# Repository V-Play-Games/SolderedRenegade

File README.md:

# SolderedRenegade

It's a Giratina which has 2 LEDs as eyes, controlled by a switch on the back!

## Author
Vaibhav Nargwani aka [@V Play Games](https://hackclub.slack.com/team/U08RM94EECT)

## Bill of Materials
| S. No.  | Name           | Quantity |
| ------- | -------------- | -------- |
| 1       | Battery Holder | 1        |
| 2       | Push Button    | 1        |
| 3       | 5mm LED        | 2        |
| 4       | Resistor       | 6        |

## Schematic

## PCB

## 3D View

Built for [Solder](https://solder.hackclub.com)!

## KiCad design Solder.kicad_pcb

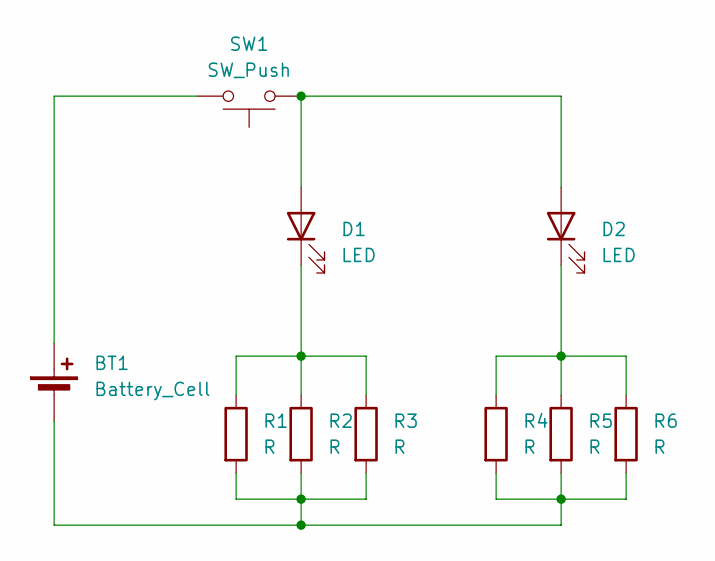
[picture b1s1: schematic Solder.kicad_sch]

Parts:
BT1: Battery_Cell; BatteryHolder_Keystone_3034_1x20mm
D1, D2: LED; LED_D5.0mm
R1, R2, R3, R4, R5, R6: R; R_Axial_DIN0207_L6.3mm_D2.5mm_P7.62mm_Horizontal
SW1: SW_Push; SW_PUSH_6mm

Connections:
unnamed: BT1.1 (+), SW1.2
unnamed: BT1.2 (-), R1.2, R2.2, R3.2, R4.2, R5.2, R6.2
unnamed: D1.2 (A), D2.2 (A), SW1.1
unnamed: D1.1 (K), R1.1, R2.1, R3.1
unnamed: D2.1 (K), R4.1, R5.1, R6.1

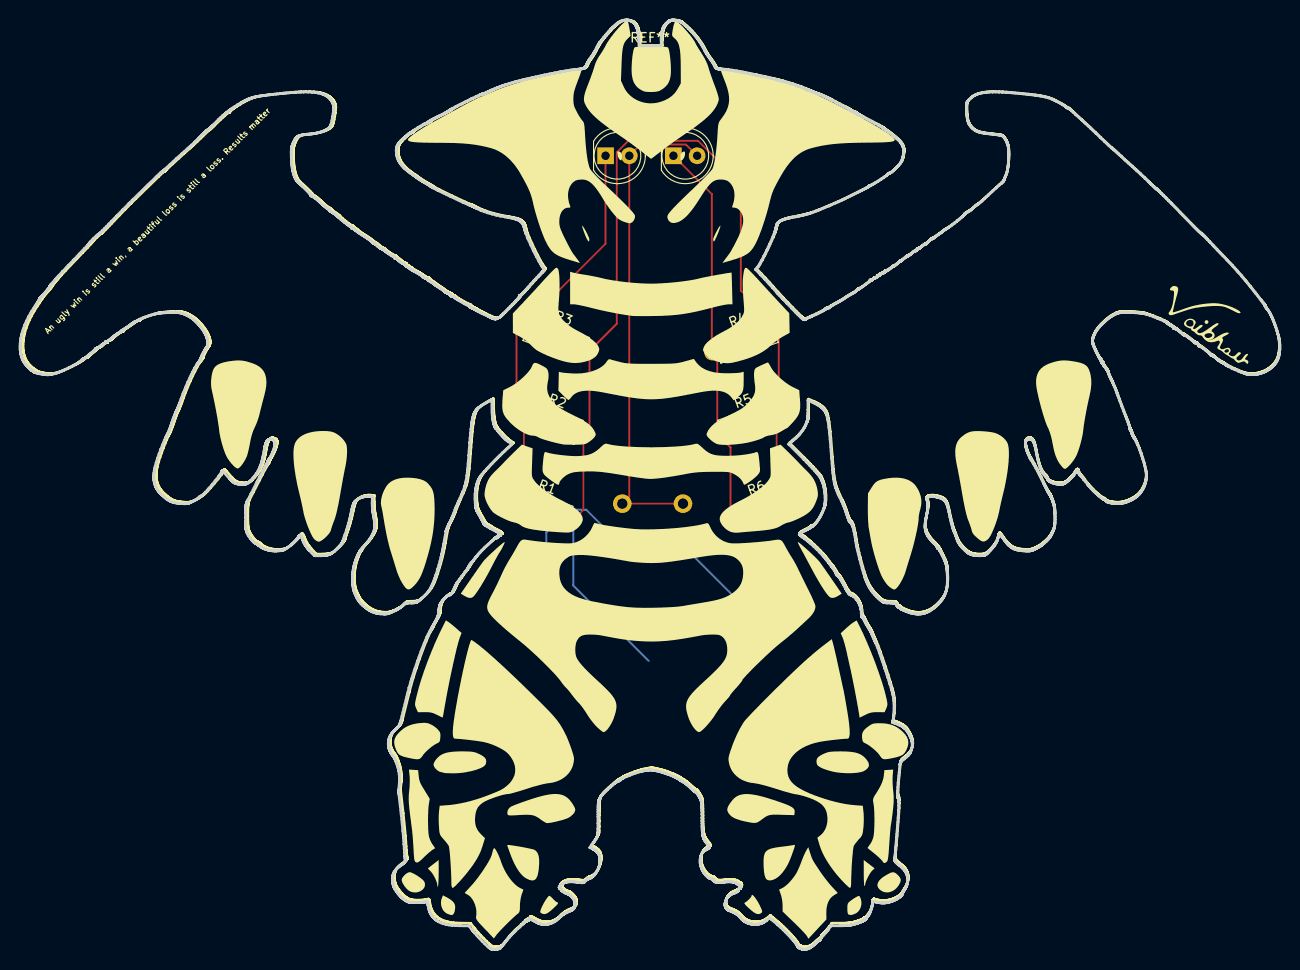
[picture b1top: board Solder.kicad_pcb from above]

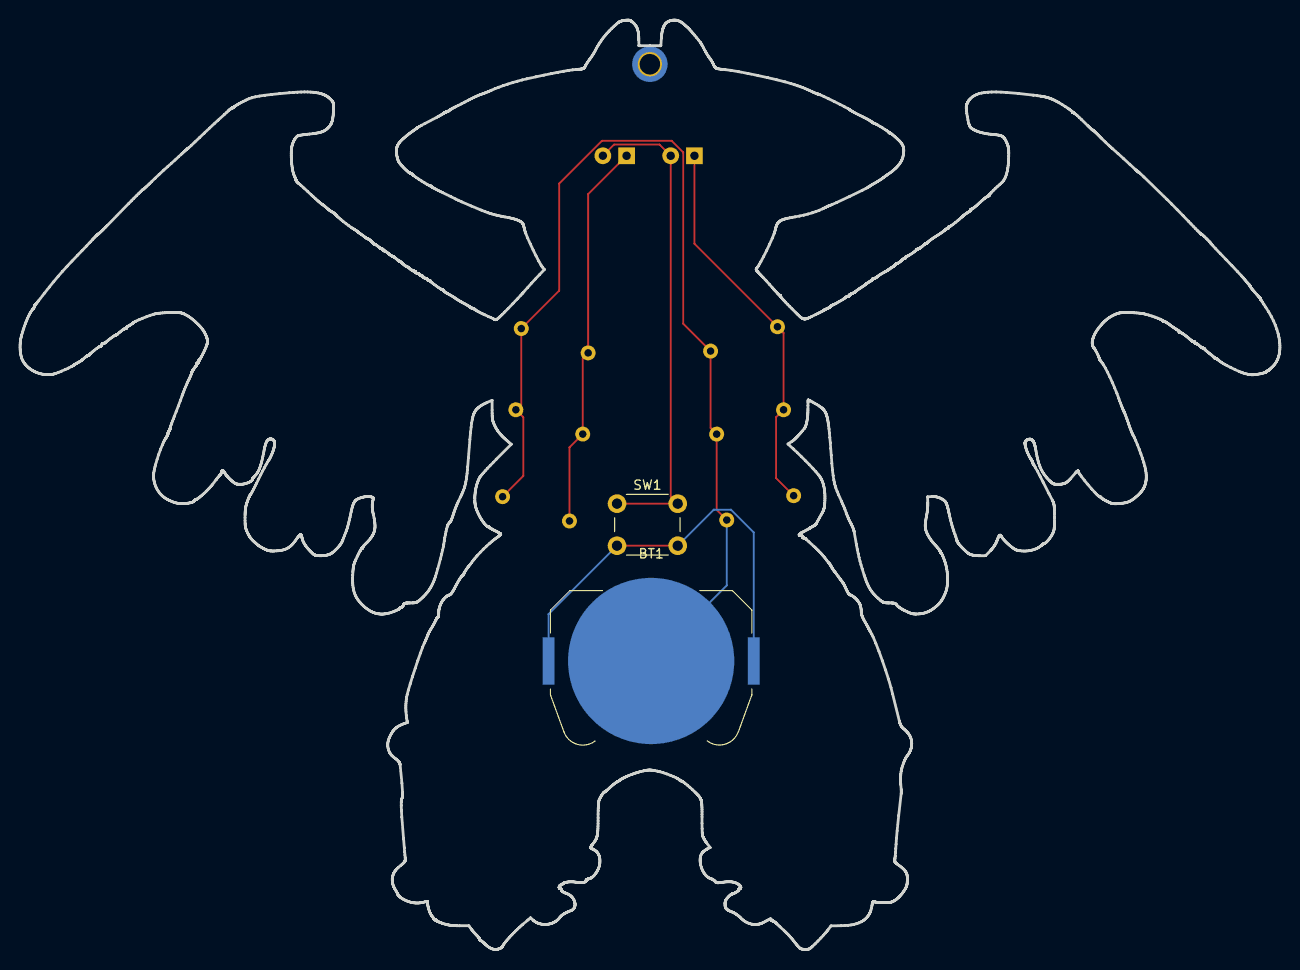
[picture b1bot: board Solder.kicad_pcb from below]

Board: 2 copper layers, 134.9 x 99.5 mm, 10 parts (2 on the bottom side), 5 nets.
